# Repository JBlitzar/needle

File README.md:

# needle

[Claude Monet](https://commons.wikimedia.org/wiki/File%3AClaude%5FMonet%5F-%5FStacks%5Fof%5FWheat%5F%28End%5Fof%5FSummer%29%5F-%5F1985.1103%5F-%5FArt%5FInstitute%5Fof%5FChicago.jpg), Public domain, via Wikimedia Commons

## Credit

[`ch32fun` submodule](firmware/ch32fun) has it's [license included](firmware/ch32fun/LICENSE)

Reference designs from datasheets in [`docs/datasheets`](docs/datasheets)

USB edge connector from here: https://github.com/vasya-zh/PCB-Edge-USB-connector-KiCad-library

some schematic components from `c57` \([license](https://raw.githubusercontent.com/cyao1234/c57/refs/heads/main/LICENSE)\)

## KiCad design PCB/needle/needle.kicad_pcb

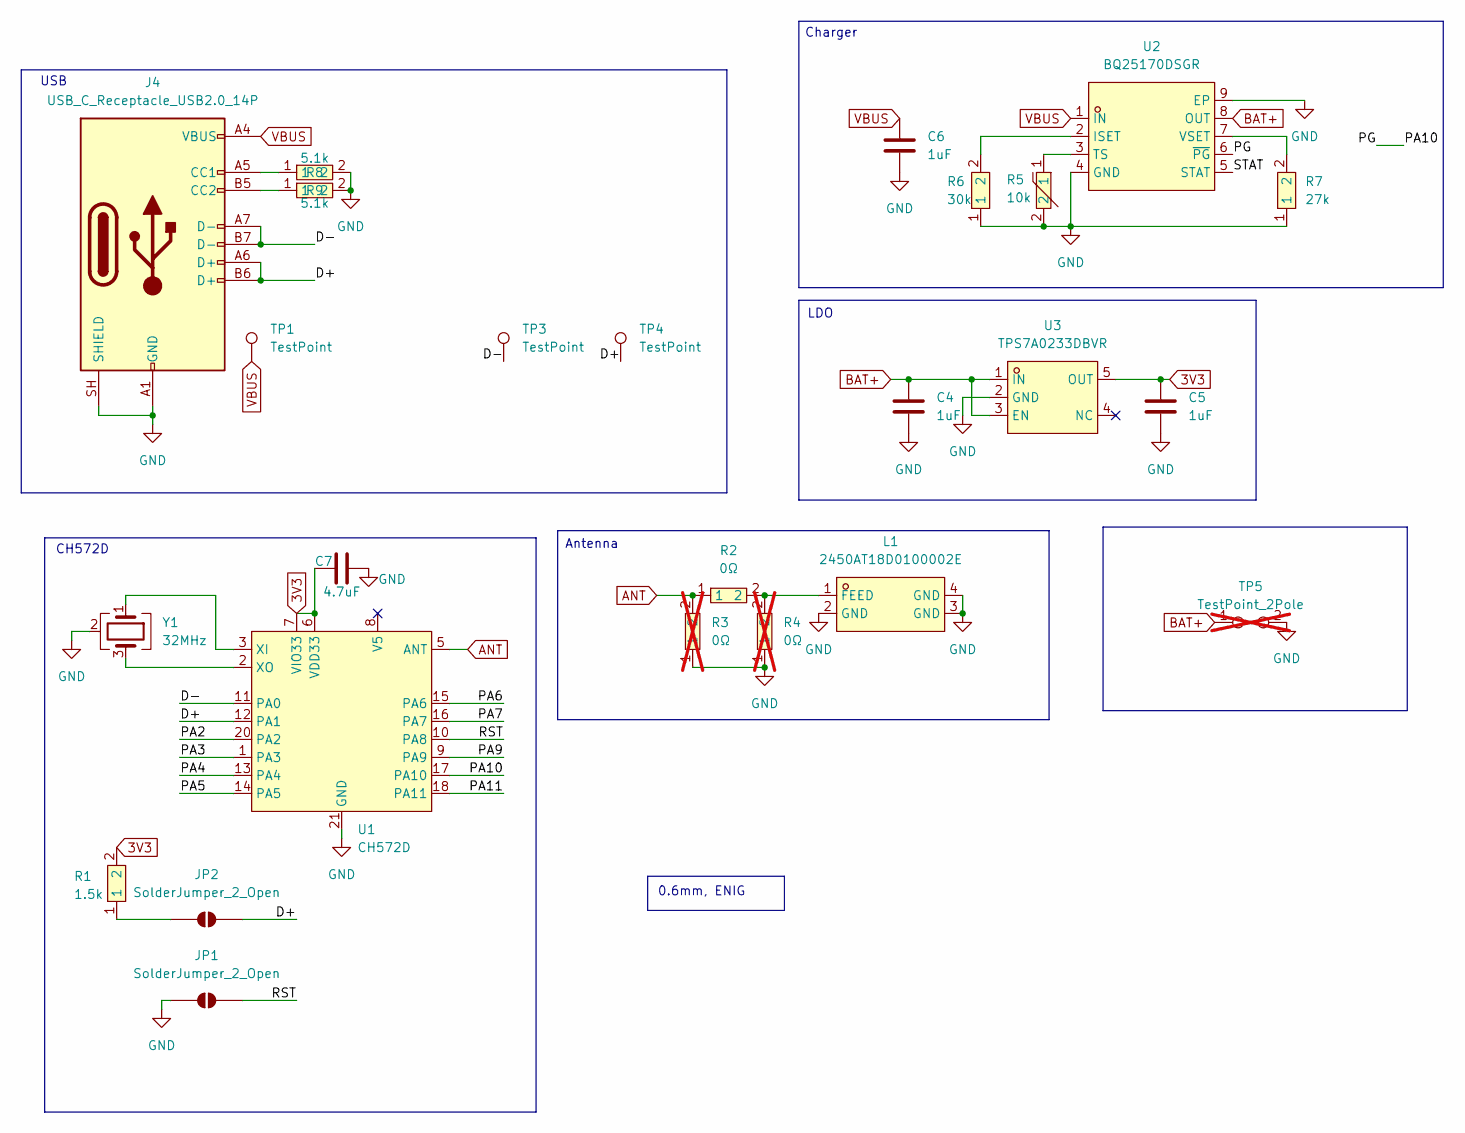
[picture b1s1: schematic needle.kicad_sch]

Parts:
C4, C5, C6: 1uF; C_0603_1608Metric; LCSC Part # C54824972
C7: 4.7uF; C_0603_1608Metric; LCSC Part # C6119851
J4: USB_C_Receptacle_USB2.0_14P; USB_C_PADDLE
JP1, JP2: SolderJumper_2_Open; SolderJumper-2_P1.3mm_Open_RoundedPad1.0x1.5mm
L1: 2450AT18D0100002E; ANT-SMD_4P-L3.2-W1.6; MPN 2450AT18D0100002E; LCSC Part C17410360
R1: 1.5k; R_0603_1608Metric; MPN FRC0603F1501TS; LCSC Part C2930050
R2: 0Ω; R_0603_1608Metric; MPN RC0603FR-070RL; LCSC Part C100044
R3, R4: 0Ω; R_0603_1608Metric; MPN RC0603FR-070RL; LCSC Part C100044; not fitted
R5: 10k; R_0603_1608Metric; MPN NCP18XH103F03RB; LCSC Part C13564
R6: 30k; R_0603_1608Metric; MPN FRC0603F3002TS; LCSC Part C2907025
R7: 27k; R_0603_1608Metric; MPN FRC0603F2702TS; LCSC Part C2930084
R8, R9: 5.1k; R_0603_1608Metric; MPN 0603WAF5101T5E; LCSC Part C23186
TP1, TP3, TP4: TestPoint; TestPoint_Pad_D1.5mm
TP5: TestPoint_2Pole; C_1206_3216Metric; not fitted
U1: CH572D; UQFN-20-1EP_3x3mm_P0.4mm_EP1.85x1.85mm_ThermalVias; LCSC Part # C46597863
U2: BQ25170DSGR; WSON-8_L2.0-W2.0-P0.50-TL-EP; MPN BQ25170DSGR; LCSC Part C5208201
U3: TPS7A0233DBVR; SOT-23-5_L2.9-W1.6-P0.95-LS2.8-BL; MPN TPS7A0233DBVR; LCSC Part C5142805
Y1: 32MHz; Crystal_SMD_2016-4Pin_2.0x1.6mm; LCSC Part # C2965584

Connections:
3V3: C5.1, C7.1, R1.2, U1.6 (VDD33), U1.7 (VIO33), U3.5 (OUT)
/D+: J4.A6 (D+), J4.B6 (D+), JP2.2 (B), TP4.1 (1_1), U1.12 (PA1)
/D-: J4.A7 (D-), J4.B7 (D-), TP3.1 (1_1), U1.11 (PA0)
/PA2: U1.20 (PA2)
/PA3: U1.1 (PA3)
/PA4: U1.13 (PA4)
/PA5: U1.14 (PA5)
/PA6: U1.15 (PA6)
/PA7: U1.16 (PA7)
/PA9: U1.9 (PA9)
/PA10: U1.17 (PA10), U2.6 (~PG)
/PA11: U1.18 (PA11)
/RST: JP1.2 (B), U1.10 (PA8)
/STAT: U2.5 (STAT)
ANT: R2.1, R3.2, U1.5 (ANT)
BAT+: C4.1, TP5.1, U2.8 (OUT), U3.1 (IN), U3.3 (EN)
GND: C4.2, C5.2, C6.2, C7.2, J4.A1 (GND), J4.A12 (GND), J4.B1 (GND), J4.B12 (GND), J4.SH (SHIELD), JP1.1 (A), L1.2 (GND), L1.3 (GND), L1.4 (GND), R3.1, R4.1, R5.2, R6.1, R7.1, R8.2, R9.2, TP5.2, U1.21 (GND), U2.4 (GND), U2.9 (EP), U3.2 (GND), Y1.2 (G), Y1.4 (G)
unnamed: J4.A5 (CC1), R8.1
unnamed: J4.B5 (CC2), R9.1
unnamed: JP2.1 (A), R1.1
unnamed: L1.1 (FEED), R2.2, R4.2
unnamed: U1.3 (XI), Y1.1
unnamed: U1.2 (XO), Y1.3
unnamed: R6.2, U2.2 (ISET)
unnamed: R5.1, U2.3 (TS)
unnamed: R7.2, U2.7 (VSET)
VBUS: C6.1, J4.A4 (VBUS), J4.A9 (VBUS), J4.B4 (VBUS), J4.B9 (VBUS), TP1.1 (1_1), U2.1 (IN)

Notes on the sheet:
0.6mm, ENIG
CH572D
Charger
LDO
Antenna
USB

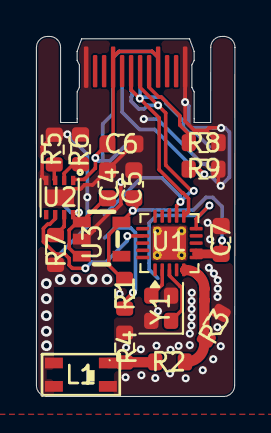
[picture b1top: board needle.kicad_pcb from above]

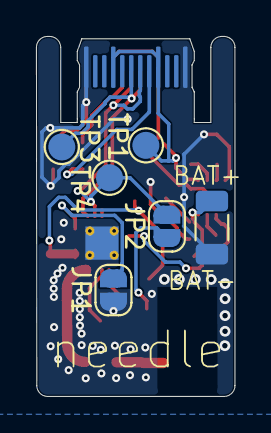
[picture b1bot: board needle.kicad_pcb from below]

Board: 2 copper layers, 11.0 x 20.0 mm, 25 parts (6 on the bottom side), 18 nets.

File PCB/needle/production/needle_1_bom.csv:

Designator,Footprint,Quantity,Value,LCSC Part #
"C4, C5, C6",0603,3,1uF,C54824972
L1,ANT-SMD_4P-L3.2-W1.6,1,2450AT18D0100002E,C17410360
R1,0603,1,1.5k,C2930050
R2,0603,1,0Ω,C100044
R5,0603,1,10k,C13564
R6,0603,1,30k,C2907025
R7,0603,1,27k,C2930084
"R8, R9",0603,2,5.1k,C23186
"TP1, TP2, TP3, TP4",TestPoint_Pad_1.5x1.5mm,4,TestPoint,
U1,UQFN-20-1EP_3x3mm_P0.4mm_EP1.85x1.85mm_ThermalVias,1,CH572D,C46597863
U2,WSON-8_L2.0-W2.0-P0.50-TL-EP,1,BQ25170DSGR,C5208201
U3,SOT-23-5_L2.9-W1.6-P0.95-LS2.8-BL,1,TPS7A0233DBVR,C5142805
Y1,Crystal_SMD_2016-4Pin_2.0x1.6mm,1,32MHz,C2965584
